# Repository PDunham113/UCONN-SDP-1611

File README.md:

# UCONN SDP 1611

## Summary

* #### Doc
  Contains various documentation and presentation on the project as a whole. This
  has NOT been curated in the slightest. Frankly, the whole project needs a
  little organization.

* #### LCD Daughterboard
  Contains EAGLE files for a graphic LCD and directional pad control. While
  ultimately scrapped, the LCD is electrically functional.

* #### Microcontroller
  Contains EAGLE files for an initial test of the SAMD21 microcontroller circuit.
  The board uses as many through-hole components as possible, and is easily
  assembled by hand. It makes an excellent low-cost substitute to other SAMD21
  development boards, despite its many shortcomings (size, USB functionality).
  Power MUST be applied via the headers, as the USB 5V line is disconnected.

* #### SDP_FIRMWARE
  Contains Arduino code for the latest firmware image for the Solid-State timer
  board. Written for ATSAMD21G18A and requires either the Arduino Zero bootloader
  or compilation by Atmel Studio.

* #### Solid State Relay
  Contains EAGLE files for an initial test of the solid-state relay circuit. The
  board uses as many through-hole components as possible and is easily assembled
  by hand. The board should be able to handle current well in excess of the screw
  terminal ratings, and is fully functional.

* #### Solid-State Timer
  Contains EAGLE files for the primary solid-state timer board. Unlike the former
  tests, this makes use of a significant number of surface mount components and
  requires some patience to assemble. A reflow oven (or toaster oven) is recommended.
  The board supports 8 devices at up to 10A each, and can control each device
  according to a preset sequence up to 240 seconds long in 0.25 second intervals.
  Serial communication over USB is supported for configuration and debugging.

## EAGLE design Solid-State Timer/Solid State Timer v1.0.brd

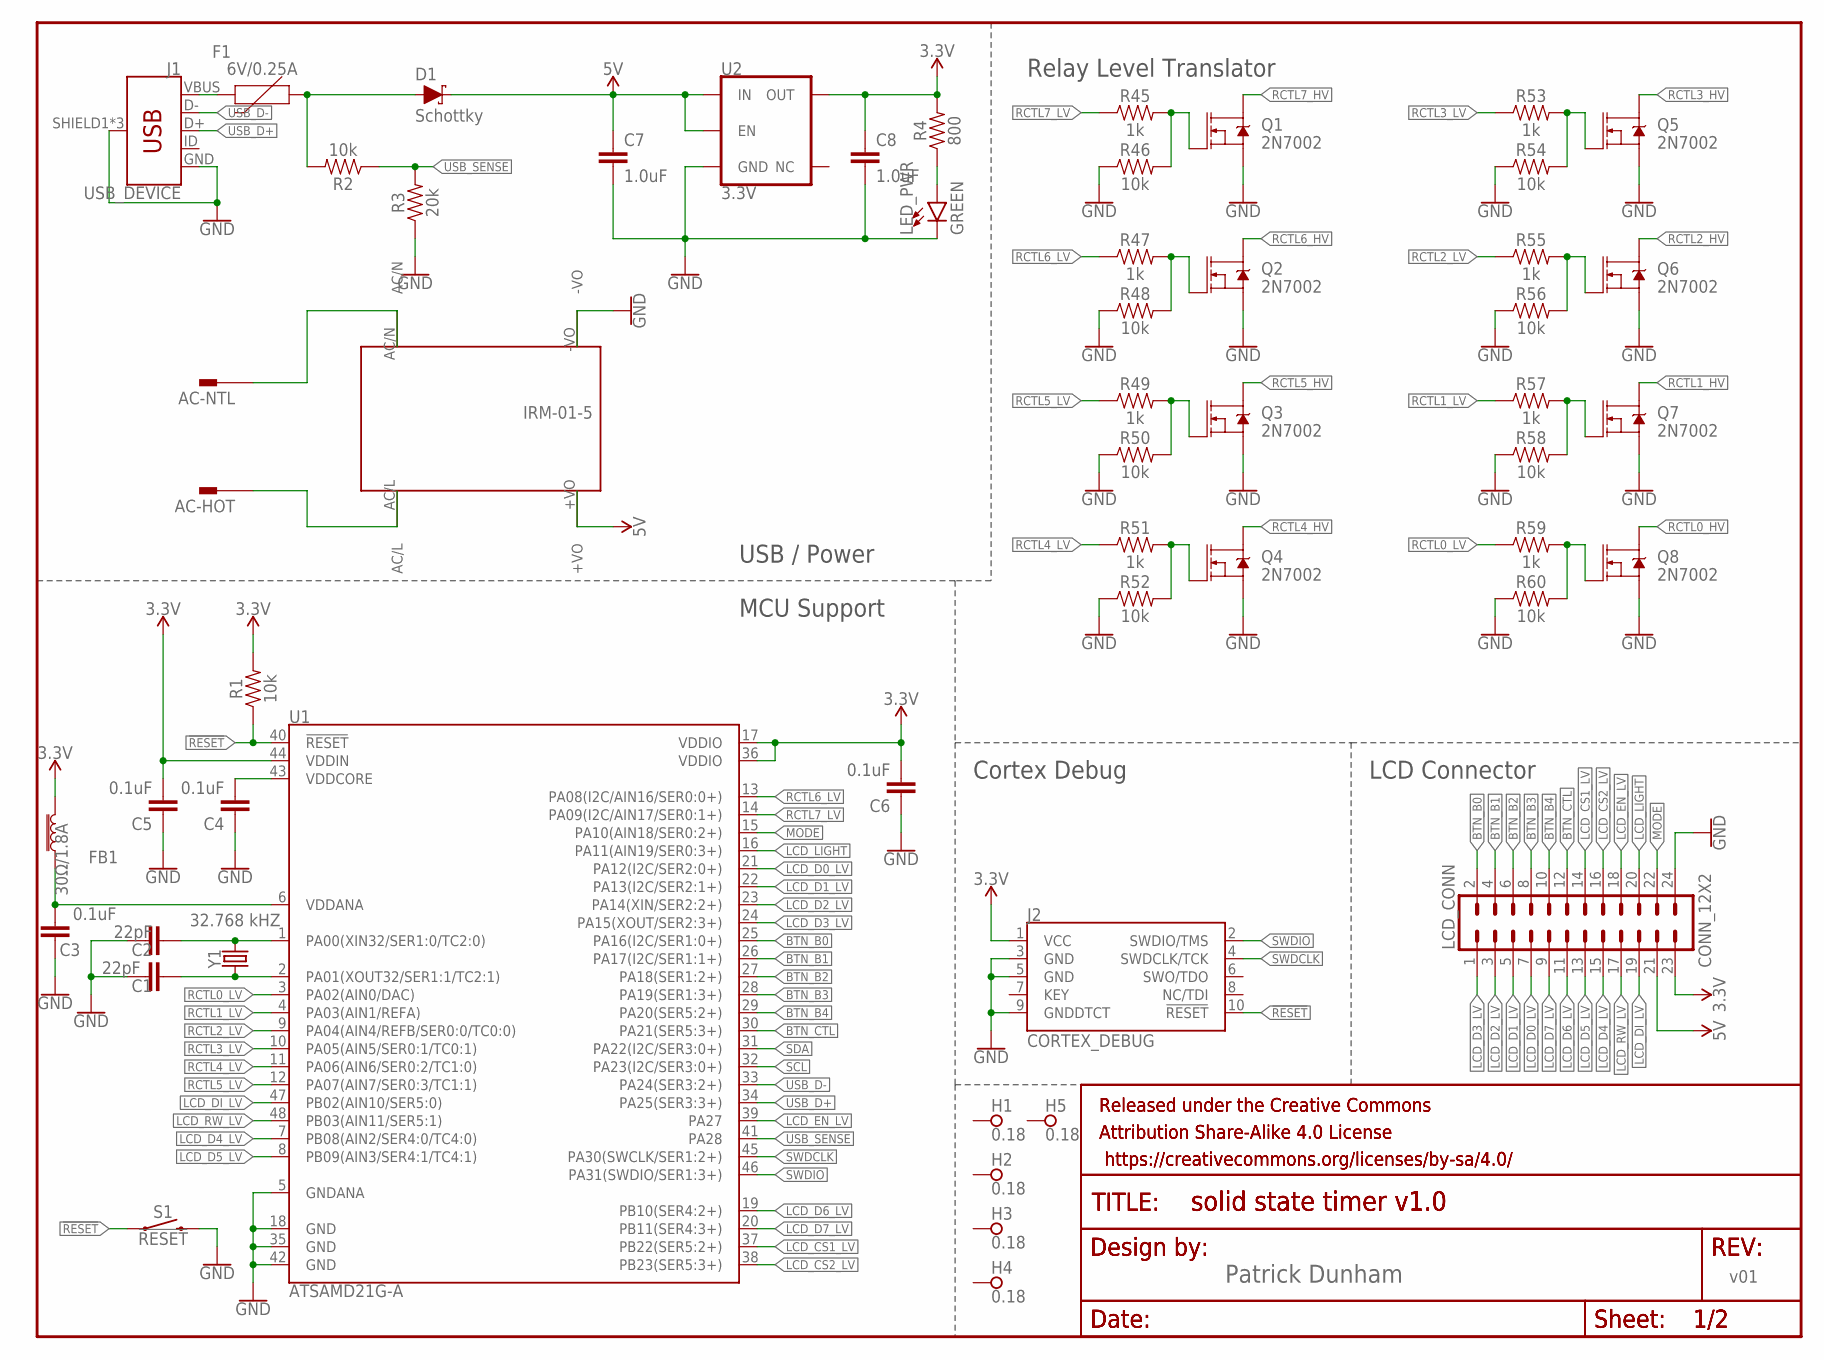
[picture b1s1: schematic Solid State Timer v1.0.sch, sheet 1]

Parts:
AC-HOT: PIN262409-1; 62409-1
AC-NTL: PIN262409-1; 62409-1
C1, C2: 22pF; 0603
C3, C4, C5, C6: 0.1uF; 0603
C7, C8: 1.0uF; 0603
D1: Schottky; SOT23-3
F1: 6V/0.25A; 1206
FB1: 30Ω/1.8A; 0603
FRAME1, FRAME3: FRAME-LETTERNO_PACKAGE; DUMMY
H1, H2, H3, H4, H5: 0.18; PAD_0.1800
J1: USB_DEVICE; USB-B-MICRO-SMD
J2: CORTEX_DEBUG; 2X5-PTH-1.27MM
LCD_CONN: CONN_12X2; 2X12
LED_PWR: GREEN; LED-0603
Q1, Q2, Q3, Q4, Q5, Q6, Q7, Q8: 2N7002; SOT323
R1, R2, R46, R48, R50, R52, R54, R56, R58, R60: 10k; 0603
R3: 20k; 0603
R4: 800; 0603
R45, R47, R49, R51, R53, R55, R57, R59: 1k; 0603
S1: !RESET; TACTILE_SWITCH_PTH_RIGHT_ANGLE_KIT
U1: ATSAMD21G-A; TQFP-48
U2: 3.3V; SOT23-5
U$1: IRM-05-1; IRM-01-5
Y1: 32.768 kHZ; CRYSTAL-SMD-3.2X1.5MM

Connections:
3.3V: C5.2, C6.2, C8.1, FB1.2, J2.1 (VCC), LCD_CONN.23, R1.2, R4.2, U1.17 (VDDIO), U1.36 (VDDIO), U1.44 (VDDIN), U2.5 (OUT); also elsewhere on the board
5V: C7.1, D1.3 (C), LCD_CONN.21, U2.1 (IN), U2.3 (EN), U$1.+VO; also elsewhere on the board
!RESET: J2.10 (!RESET), R1.1, S1.1, U1.40 (!RESET!)
BTN_B0: LCD_CONN.2, U1.25 (PA16(I2C/SER1:0+))
BTN_B1: LCD_CONN.4, U1.26 (PA17(I2C/SER1:1+))
BTN_B2: LCD_CONN.6, U1.27 (PA18(SER1:2+))
BTN_B3: LCD_CONN.8, U1.28 (PA19(SER1:3+))
BTN_B4: LCD_CONN.10, U1.29 (PA20(SER5:2+))
BTN_CTL: LCD_CONN.12, U1.30 (PA21(SER5:3+))
GND: C1.1, C2.1, C3.1, C4.1, C5.1, C6.1, C7.2, C8.2, J1.GND, J1.SHIELD1 (SHIELD), J1.SHIELD2 (SHIELD), J1.SHIELD3 (SHIELD), J2.3 (GND), J2.5 (GND), J2.9 (GNDDTCT), LCD_CONN.24, LED_PWR.C, Q1.2 (S), Q2.2 (S), Q3.2 (S), Q4.2 (S), Q5.2 (S), Q6.2 (S), Q7.2 (S), Q8.2 (S), R3.1, R46.1, R48.1, R50.1, R52.1, R54.1, R56.1, R58.1, R60.1, S1.2, U1.5 (GNDANA), U1.18 (GND), U1.35 (GND), U1.42 (GND), U2.2 (GND), U$1.-VO; also elsewhere on the board
LCD_CS1_LV: LCD_CONN.14, U1.37 (PB22(SER5:2+))
LCD_CS2_LV: LCD_CONN.16, U1.38 (PB23(SER5:3+))
LCD_D0_LV: LCD_CONN.7, U1.21 (PA12(I2C/SER2:0+))
LCD_D1_LV: LCD_CONN.5, U1.22 (PA13(I2C/SER2:1+))
LCD_D2_LV: LCD_CONN.3, U1.23 (PA14(XIN/SER2:2+))
LCD_D3_LV: LCD_CONN.1, U1.24 (PA15(XOUT/SER2:3+))
LCD_D4_LV: LCD_CONN.15, U1.7 (PB08(AIN2/SER4:0/TC4:0))
LCD_D5_LV: LCD_CONN.13, U1.8 (PB09(AIN3/SER4:1/TC4:1))
LCD_D6_LV: LCD_CONN.11, U1.19 (PB10(SER4:2+))
LCD_D7_LV: LCD_CONN.9, U1.20 (PB11(SER4:3+))
LCD_DI_LV: LCD_CONN.19, U1.47 (PB02(AIN10/SER5:0))
LCD_EN_LV: LCD_CONN.18, U1.39 (PA27)
LCD_LIGHT: LCD_CONN.20, U1.16 (PA11(AIN19/SER0:3+))
LCD_RW_LV: LCD_CONN.17, U1.48 (PB03(AIN11/SER5:1))
MODE: LCD_CONN.22, U1.15 (PA10(AIN18/SER0:2+))
unnamed: C2.2, U1.1 (PA00(XIN32/SER1:0/TC2:0)), Y1.P$2 (2)
unnamed: C1.2, U1.2 (PA01(XOUT32/SER1:1/TC2:1)), Y1.P$1 (1)
unnamed: C3.2, FB1.1, U1.6 (VDDANA)
unnamed: C4.2, U1.43 (VDDCORE)
unnamed: F1.2, J1.VBUS
unnamed: AC-NTL.A1, AC-NTL.A2, U$1.AC/N
unnamed: AC-HOT.A1, AC-HOT.A2, U$1.AC/L
unnamed: LED_PWR.A, R4.1
unnamed: Q1.1 (G), R45.2, R46.2
unnamed: D1.1 (A), F1.1, R2.2
unnamed: Q2.1 (G), R47.2, R48.2
unnamed: Q3.1 (G), R49.2, R50.2
unnamed: Q4.1 (G), R51.2, R52.2
unnamed: Q5.1 (G), R53.2, R54.2
unnamed: Q6.1 (G), R55.2, R56.2
unnamed: Q7.1 (G), R57.2, R58.2
unnamed: Q8.1 (G), R59.2, R60.2
RCTL0_HV: Q8.3 (D); also elsewhere on the board
RCTL0_LV: R59.1, U1.3 (PA02(AIN0/DAC))
RCTL1_HV: Q7.3 (D); also elsewhere on the board
RCTL1_LV: R57.1, U1.4 (PA03(AIN1/REFA))
RCTL2_HV: Q6.3 (D); also elsewhere on the board
RCTL2_LV: R55.1, U1.9 (PA04(AIN4/REFB/SER0:0/TC0:0))
RCTL3_HV: Q5.3 (D); also elsewhere on the board
RCTL3_LV: R53.1, U1.10 (PA05(AIN5/SER0:1/TC0:1))
RCTL4_HV: Q4.3 (D); also elsewhere on the board
RCTL4_LV: R51.1, U1.11 (PA06(AIN6/SER0:2/TC1:0))
RCTL5_HV: Q3.3 (D); also elsewhere on the board
RCTL5_LV: R49.1, U1.12 (PA07(AIN7/SER0:3/TC1:1))
RCTL6_HV: Q2.3 (D); also elsewhere on the board
RCTL6_LV: R47.1, U1.13 (PA08(I2C/AIN16/SER0:0+))
RCTL7_HV: Q1.3 (D); also elsewhere on the board
RCTL7_LV: R45.1, U1.14 (PA09(I2C/AIN17/SER0:1+))
SCL: U1.32 (PA23(I2C/SER3:0+)); also elsewhere on the board
SDA: U1.31 (PA22(I2C/SER3:0+)); also elsewhere on the board
SWDCLK: J2.4 (SWDCLK/TCK), U1.45 (PA30(SWCLK/SER1:2+))
SWDIO: J2.2 (SWDIO/TMS), U1.46 (PA31(SWDIO/SER1:3+))
USB_D+: J1.D+, U1.34 (PA25(SER3:3+))
USB_D-: J1.D-, U1.33 (PA24(SER3:2+))
USB_SENSE: R2.1, R3.2, U1.41 (PA28)

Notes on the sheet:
MCU Support
Cortex Debug
USB / Power
LCD Connector
Relay Level Translator

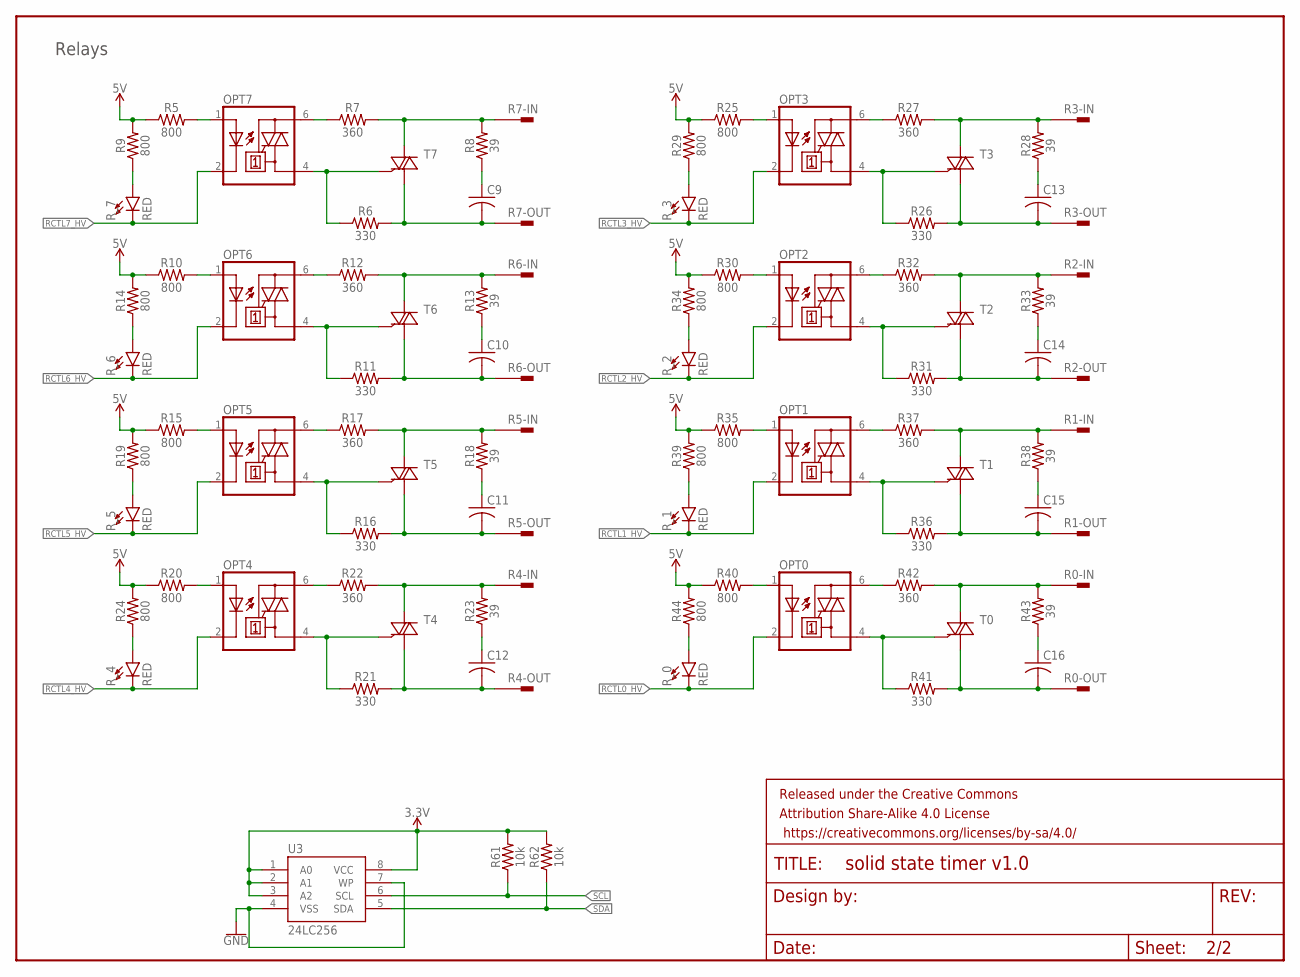
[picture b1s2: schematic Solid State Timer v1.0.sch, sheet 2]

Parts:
C9, C10, C11, C12, C13, C14, C15, C16: C-USC1206; C1206
FRAME2: FRAME-LETTERNO_PACKAGE; DUMMY
OPT0, OPT1, OPT2, OPT3, OPT4, OPT5, OPT6, OPT7: MOC3031M; DIL06
R0-IN, R0-OUT, R1-IN, R1-OUT, R2-IN, R2-OUT, R3-IN, R3-OUT, R4-IN, R4-OUT, R5-IN, R5-OUT, R6-IN, R6-OUT, R7-IN, R7-OUT: PIN262409-1; 62409-1
R5, R9, R10, R14, R15, R19, R20, R24, R25, R29, R30, R34, R35, R39, R40, R44: 800; 0603
R6, R11, R16, R21, R26, R31, R36, R41: 330; 0603
R7, R12, R17, R22, R27, R32, R37, R42: 360; 0603
R8, R13, R18, R23, R28, R33, R38, R43: 39; 0603
R61, R62: 10k; 0603
R_0, R_1, R_2, R_3, R_4, R_5, R_6, R_7: RED; LED-0603
T0, T1, T2, T3, T4, T5, T6, T7: BT138-V; TO220BV
U3: 24LC256; SO08

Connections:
3.3V: R61.2, R62.2, U3.1 (A0), U3.2 (A1), U3.3 (A2), U3.8 (VCC); also elsewhere on the board
5V: R5.1, R9.2, R10.1, R14.2, R15.1, R19.2, R20.1, R24.2, R25.1, R29.2, R30.1, R34.2, R35.1, R39.2, R40.1, R44.2; also elsewhere on the board
GND: U3.4 (VSS), U3.7 (WP); also elsewhere on the board
unnamed: OPT7.1 (A), R5.2
unnamed: OPT7.4 (A1), R6.1, T7.G
unnamed: OPT7.6 (A2), R7.1
unnamed: R7.2, R7-IN.A1, R7-IN.A2, R8.2, T7.T2 (A2)
unnamed: C9.1, R8.1
unnamed: C9.2, R6.2, R7-OUT.A1, R7-OUT.A2, T7.T1 (A1)
unnamed: R9.1, R_7.A
unnamed: OPT6.1 (A), R10.2
unnamed: OPT6.4 (A1), R11.1, T6.G
unnamed: OPT6.6 (A2), R12.1
unnamed: R6-IN.A1, R6-IN.A2, R12.2, R13.2, T6.T2 (A2)
unnamed: C10.1, R13.1
unnamed: C10.2, R6-OUT.A1, R6-OUT.A2, R11.2, T6.T1 (A1)
unnamed: R14.1, R_6.A
unnamed: OPT5.1 (A), R15.2
unnamed: OPT5.4 (A1), R16.1, T5.G
unnamed: OPT5.6 (A2), R17.1
unnamed: R5-IN.A1, R5-IN.A2, R17.2, R18.2, T5.T2 (A2)
unnamed: C11.1, R18.1
unnamed: C11.2, R5-OUT.A1, R5-OUT.A2, R16.2, T5.T1 (A1)
unnamed: R19.1, R_5.A
unnamed: OPT4.1 (A), R20.2
unnamed: OPT4.4 (A1), R21.1, T4.G
unnamed: OPT4.6 (A2), R22.1
unnamed: R4-IN.A1, R4-IN.A2, R22.2, R23.2, T4.T2 (A2)
unnamed: C12.1, R23.1
unnamed: C12.2, R4-OUT.A1, R4-OUT.A2, R21.2, T4.T1 (A1)
unnamed: R24.1, R_4.A
unnamed: OPT3.1 (A), R25.2
unnamed: OPT3.4 (A1), R26.1, T3.G
unnamed: OPT3.6 (A2), R27.1
unnamed: R3-IN.A1, R3-IN.A2, R27.2, R28.2, T3.T2 (A2)
unnamed: C13.1, R28.1
unnamed: R29.1, R_3.A
unnamed: OPT2.1 (A), R30.2
unnamed: OPT2.4 (A1), R31.1, T2.G
unnamed: OPT2.6 (A2), R32.1
unnamed: R2-IN.A1, R2-IN.A2, R32.2, R33.2, T2.T2 (A2)
unnamed: C14.1, R33.1
unnamed: C14.2, R2-OUT.A1, R2-OUT.A2, R31.2, T2.T1 (A1)
unnamed: R34.1, R_2.A
unnamed: OPT1.1 (A), R35.2
unnamed: OPT1.4 (A1), R36.1, T1.G
unnamed: OPT1.6 (A2), R37.1
unnamed: R1-IN.A1, R1-IN.A2, R37.2, R38.2, T1.T2 (A2)
unnamed: C15.1, R38.1
unnamed: C15.2, R1-OUT.A1, R1-OUT.A2, R36.2, T1.T1 (A1)
unnamed: R39.1, R_1.A
unnamed: OPT0.1 (A), R40.2
unnamed: OPT0.4 (A1), R41.1, T0.G
unnamed: OPT0.6 (A2), R42.1
unnamed: R0-IN.A1, R0-IN.A2, R42.2, R43.2, T0.T2 (A2)
unnamed: C16.1, R43.1
unnamed: C16.2, R0-OUT.A1, R0-OUT.A2, R41.2, T0.T1 (A1)
unnamed: R44.1, R_0.A
R3-OUT: C13.2, R3-OUT.A1, R3-OUT.A2, R26.2, T3.T1 (A1)
RCTL0_HV: OPT0.2 (C), R_0.C; also elsewhere on the board
RCTL1_HV: OPT1.2 (C), R_1.C; also elsewhere on the board
RCTL2_HV: OPT2.2 (C), R_2.C; also elsewhere on the board
RCTL3_HV: OPT3.2 (C), R_3.C; also elsewhere on the board
RCTL4_HV: OPT4.2 (C), R_4.C; also elsewhere on the board
RCTL5_HV: OPT5.2 (C), R_5.C; also elsewhere on the board
RCTL6_HV: OPT6.2 (C), R_6.C; also elsewhere on the board
RCTL7_HV: OPT7.2 (C), R_7.C; also elsewhere on the board
SCL: R61.1, U3.6 (SCL); also elsewhere on the board
SDA: R62.1, U3.5 (SDA); also elsewhere on the board

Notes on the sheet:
Relays

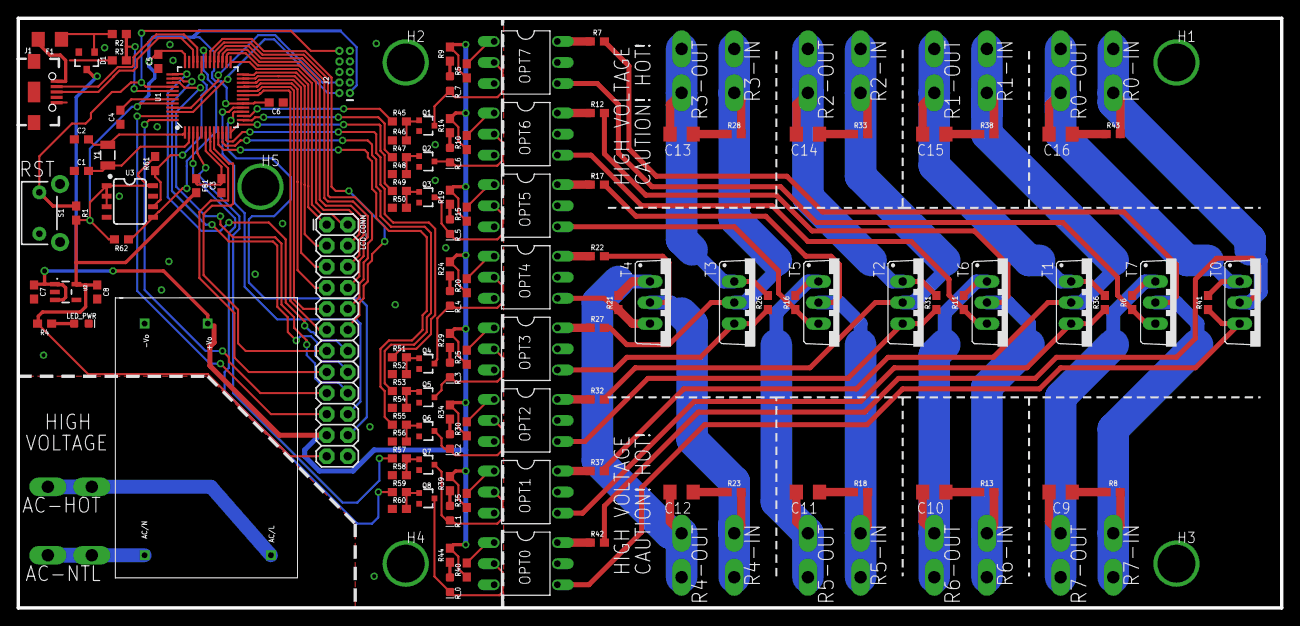
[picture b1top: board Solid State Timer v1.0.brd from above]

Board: 2 copper layers, 152.4 x 71.1 mm, 149 parts (0 on the bottom side), 121 nets.

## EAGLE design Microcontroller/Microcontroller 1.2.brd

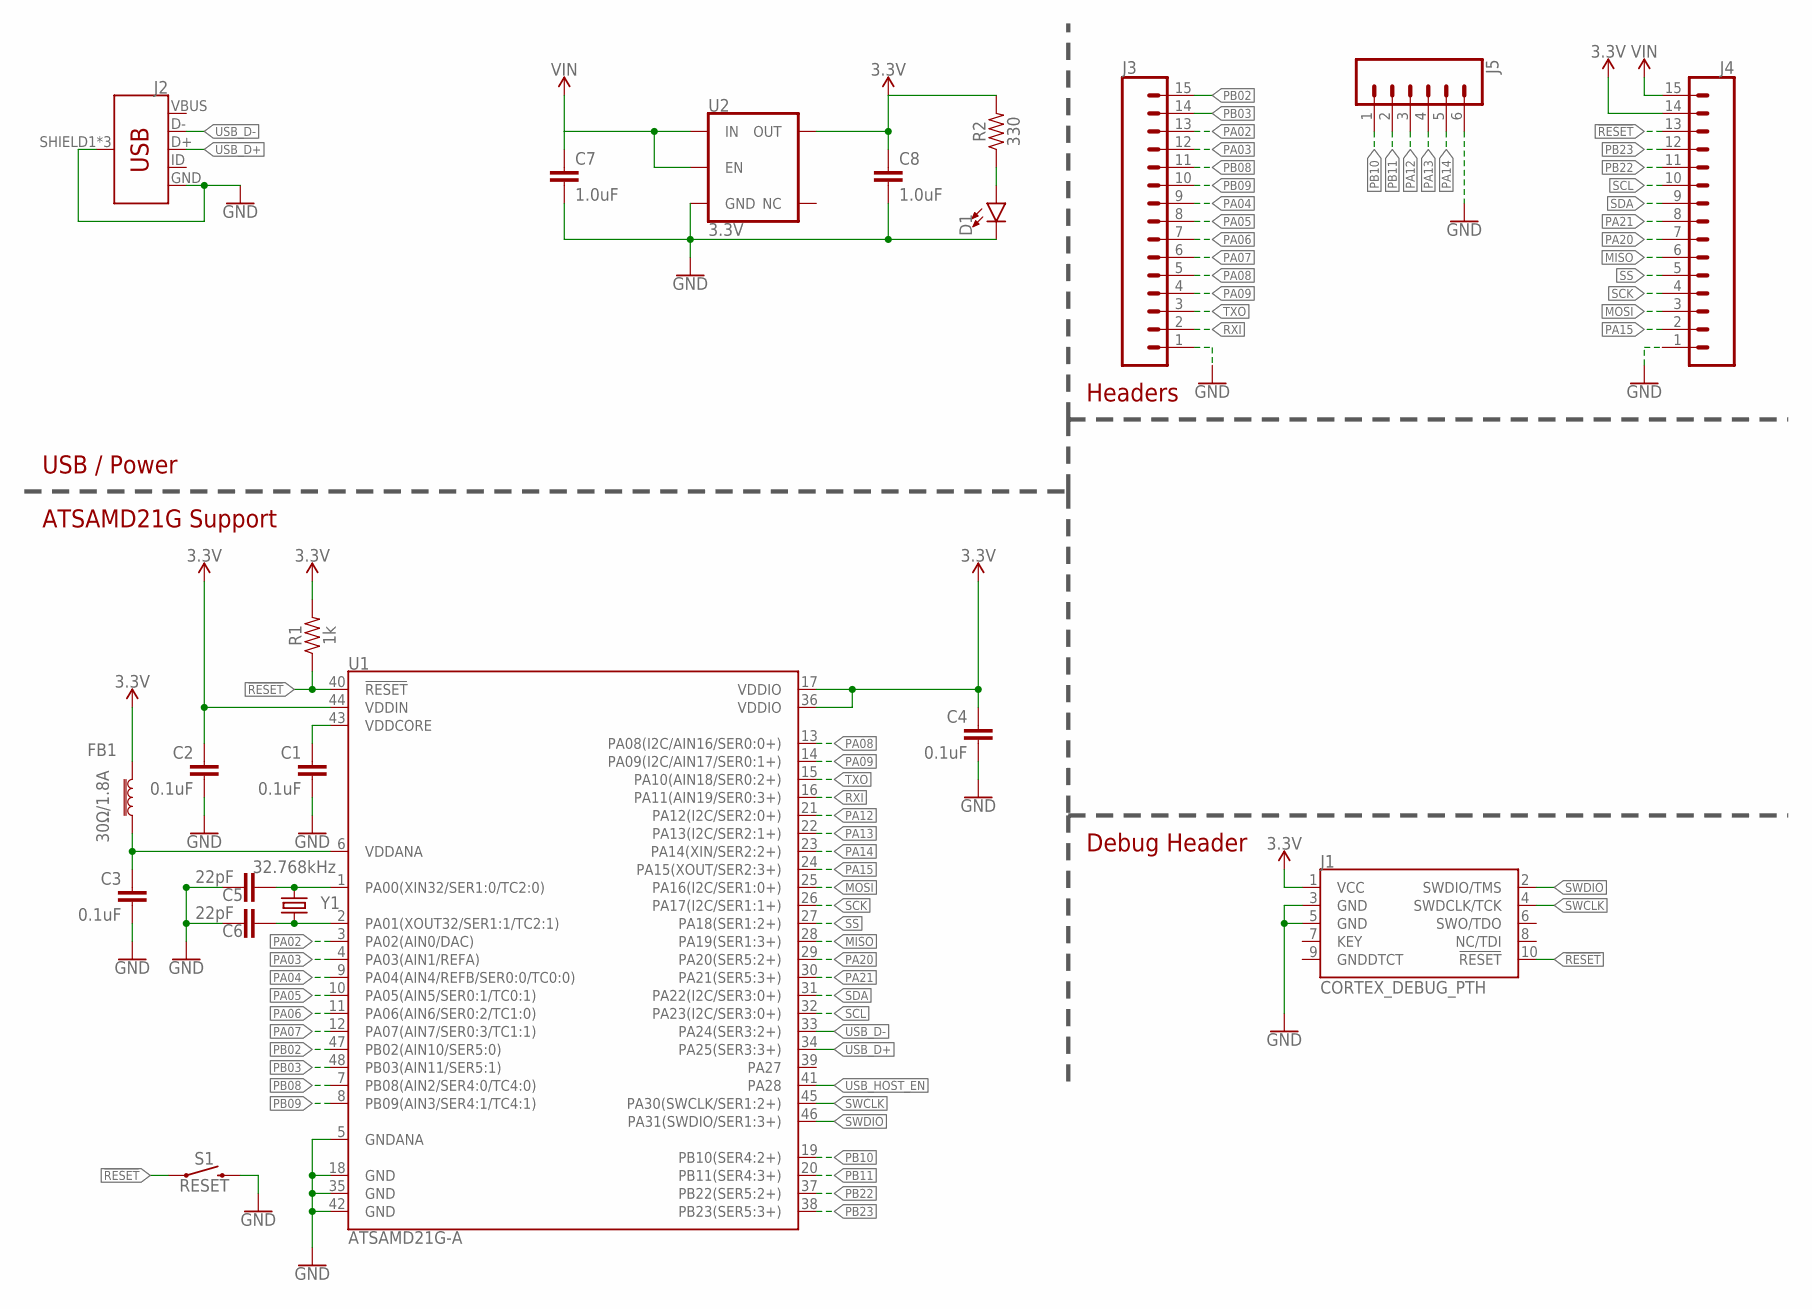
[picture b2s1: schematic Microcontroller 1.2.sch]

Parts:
C1, C2, C3, C4: 0.1uF; CAP-PTH-SMALL-KIT
C5, C6: 22pF; CAP-PTH-SMALL-KIT
C7, C8: 1.0uF; CAP-PTH-SMALL-KIT
D1: LED5MM; LED_5MM
FB1: 30Ω/1.8A; 0603
J1: CORTEX_DEBUG_PTH; 2X5-PTH-1.27MM
J2: USB_MICRO-B_FEMALE-SMT; USB-B-MICRO-SMD
J3, J4: CONN_15LOCK; 1X15_LOCK
J5: CONN_06LOCK; 1X06_LOCK
R1: 1k; AXIAL-0.3
R2: 330; AXIAL-0.3
S1: RESET; TACTILE_SWITCH_PTH_RIGHT_ANGLE_KIT
U1: ATSAMD21G-A; TQFP-48
U2: 3.3V; SOT23-5
Y1: 32.768kHz; CRYSTAL-PTH-2X6-CYL

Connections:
3.3V: C2.1, C4.1, C8.1, FB1.1, J1.1 (VCC), J4.14, R1.P$2 (2), R2.P$2 (2), U1.17 (VDDIO), U1.36 (VDDIO), U1.44 (VDDIN), U2.5 (OUT)
!RESET: J1.10 (!RESET), J4.13, R1.P$1 (1), S1.1, U1.40 (!RESET!)
GND: C1.2, C2.2, C3.2, C4.2, C5.1, C6.1, C7.2, C8.2, D1.K (C), J1.3 (GND), J1.5 (GND), J2.GND, J2.SHIELD1 (SHIELD), J2.SHIELD2 (SHIELD), J2.SHIELD3 (SHIELD), J3.1, J4.1, J5.6, S1.2, U1.5 (GNDANA), U1.18 (GND), U1.35 (GND), U1.42 (GND), U2.2 (GND)
MISO: J4.6, U1.28 (PA19(SER1:3+))
MOSI: J4.3, U1.25 (PA16(I2C/SER1:0+))
unnamed: C1.1, U1.43 (VDDCORE)
unnamed: C6.2, U1.2 (PA01(XOUT32/SER1:1/TC2:1)), Y1.1
unnamed: C3.1, FB1.2, U1.6 (VDDANA)
unnamed: C5.2, U1.1 (PA00(XIN32/SER1:0/TC2:0)), Y1.2
unnamed: D1.A, R2.P$1 (1)
PA02: J3.13, U1.3 (PA02(AIN0/DAC))
PA03: J3.12, U1.4 (PA03(AIN1/REFA))
PA04: J3.9, U1.9 (PA04(AIN4/REFB/SER0:0/TC0:0))
PA05: J3.8, U1.10 (PA05(AIN5/SER0:1/TC0:1))
PA06: J3.7, U1.11 (PA06(AIN6/SER0:2/TC1:0))
PA07: J3.6, U1.12 (PA07(AIN7/SER0:3/TC1:1))
PA08: J3.5, U1.13 (PA08(I2C/AIN16/SER0:0+))
PA09: J3.4, U1.14 (PA09(I2C/AIN17/SER0:1+))
PA12: J5.3, U1.21 (PA12(I2C/SER2:0+))
PA13: J5.4, U1.22 (PA13(I2C/SER2:1+))
PA14: J5.5, U1.23 (PA14(XIN/SER2:2+))
PA15: J4.2, U1.24 (PA15(XOUT/SER2:3+))
PA20: J4.7, U1.29 (PA20(SER5:2+))
PA21: J4.8, U1.30 (PA21(SER5:3+))
PB02: J3.15, U1.47 (PB02(AIN10/SER5:0))
PB03: J3.14, U1.48 (PB03(AIN11/SER5:1))
PB08: J3.11, U1.7 (PB08(AIN2/SER4:0/TC4:0))
PB09: J3.10, U1.8 (PB09(AIN3/SER4:1/TC4:1))
PB10: J5.1, U1.19 (PB10(SER4:2+))
PB11: J5.2, U1.20 (PB11(SER4:3+))
PB22: J4.11, U1.37 (PB22(SER5:2+))
PB23: J4.12, U1.38 (PB23(SER5:3+))
RXI: J3.2, U1.16 (PA11(AIN19/SER0:3+))
SCK: J4.4, U1.26 (PA17(I2C/SER1:1+))
SCL: J4.10, U1.32 (PA23(I2C/SER3:0+))
SDA: J4.9, U1.31 (PA22(I2C/SER3:0+))
SS: J4.5, U1.27 (PA18(SER1:2+))
SWCLK: J1.4 (SWDCLK/TCK), U1.45 (PA30(SWCLK/SER1:2+))
SWDIO: J1.2 (SWDIO/TMS), U1.46 (PA31(SWDIO/SER1:3+))
TXO: J3.3, U1.15 (PA10(AIN18/SER0:2+))
USB_D+: J2.D+, U1.34 (PA25(SER3:3+))
USB_D-: J2.D-, U1.33 (PA24(SER3:2+))
USB_HOST_EN: U1.41 (PA28)
VBUS: J2.VBUS
VIN: C7.1, J4.15, U2.1 (IN), U2.3 (EN)

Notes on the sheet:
ATSAMD21G Support
Debug Header
Headers
USB / Power

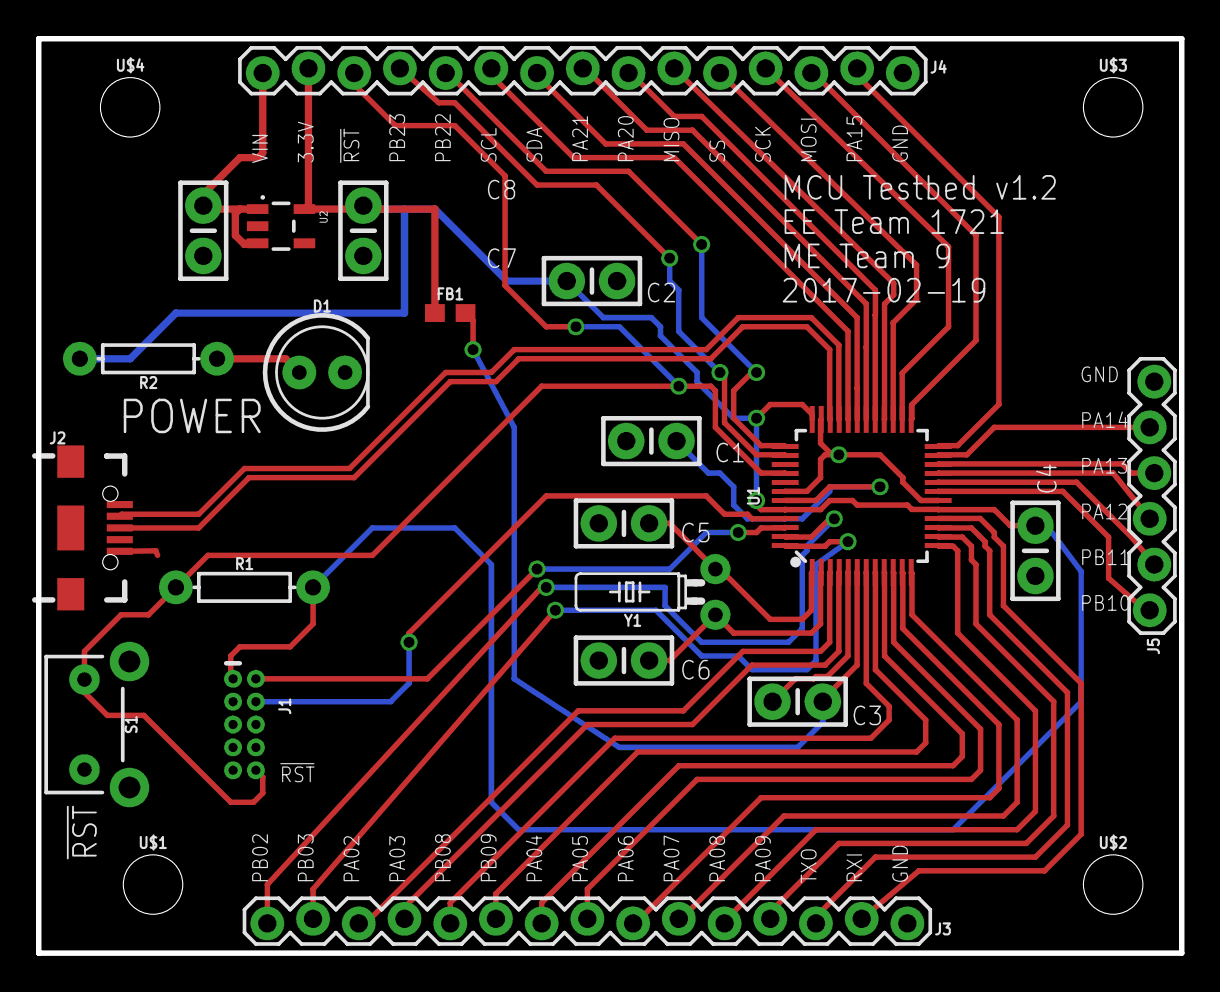
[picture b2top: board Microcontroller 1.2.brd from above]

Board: 2 copper layers, 63.5 x 50.8 mm, 25 parts (0 on the bottom side), 43 nets.

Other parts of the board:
U$1, U$2, U$3, U$4: STAND-OFF

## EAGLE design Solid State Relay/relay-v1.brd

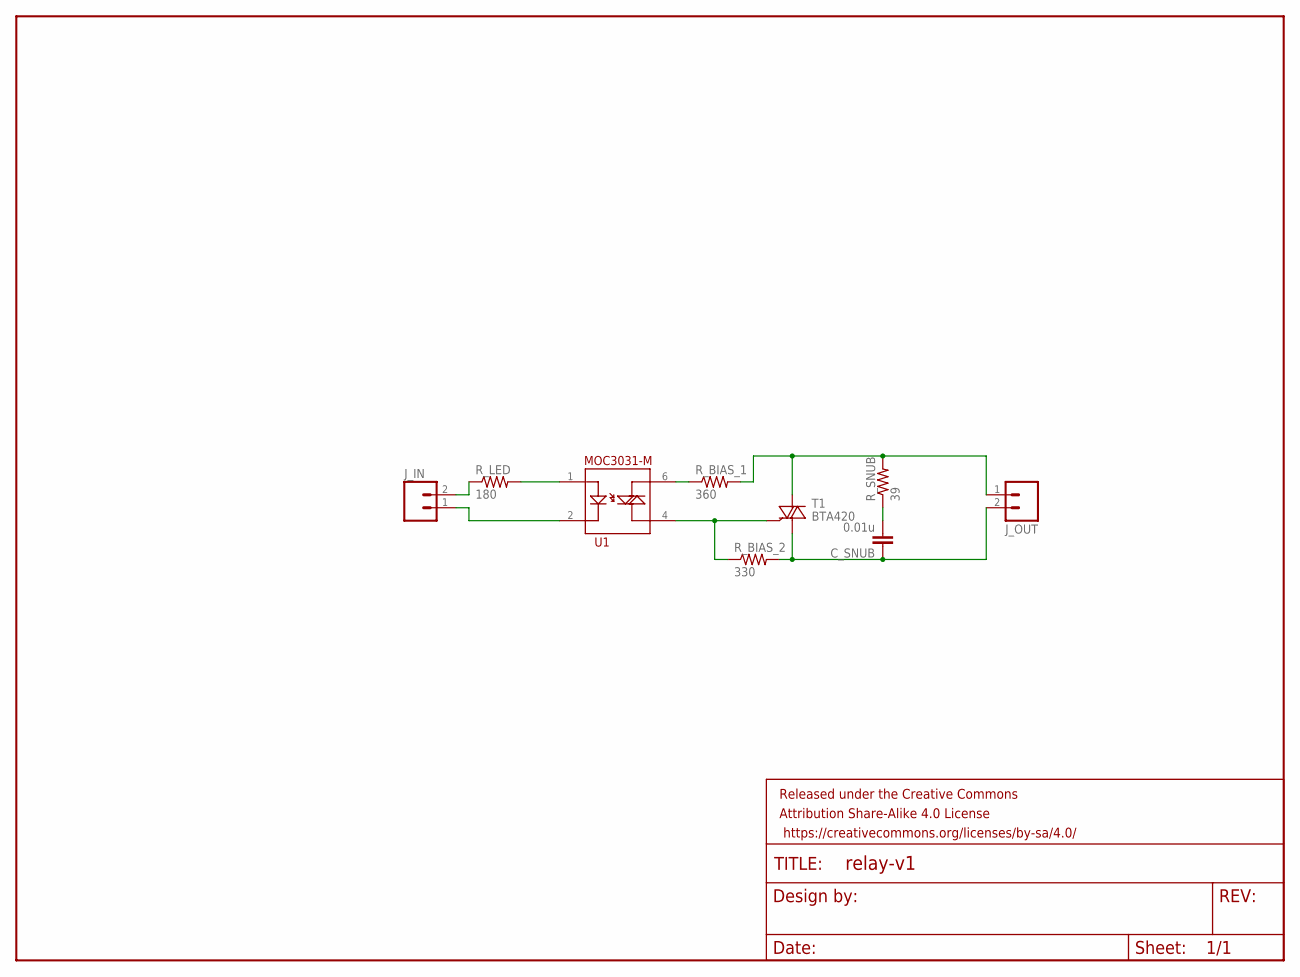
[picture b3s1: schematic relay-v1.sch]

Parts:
C_SNUB: 0.01u; CAP-PTH-SMALLEZ
FRAME1: FRAME-LETTERNO_PACKAGE; DUMMY
J_IN: M02PTH; 1X02
J_OUT: M025MM; SCREWTERMINAL-5MM-2
R_BIAS_1: 360; AXIAL-0.4
R_BIAS_2: 330; AXIAL-0.4
R_LED: 180; AXIAL-0.4
R_SNUB: 39; AXIAL-0.4
T1: BTA420; TO220BV
U1: MOC3063M; DIL06

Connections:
DEVICE: J_OUT.1, R_BIAS_1.P$2 (2), R_SNUB.P$2 (2), T1.T2 (A2)
LED_MINUS: J_IN.1, U1.2
LED_PLUS: J_IN.2, R_LED.P$1 (1)
unnamed: R_LED.P$2 (2), U1.1
unnamed: R_BIAS_1.P$1 (1), U1.6
unnamed: R_BIAS_2.P$1 (1), T1.G, U1.4
unnamed: C_SNUB.2, R_SNUB.P$1 (1)
POWER: C_SNUB.1, J_OUT.2, R_BIAS_2.P$2 (2), T1.T1 (A1)

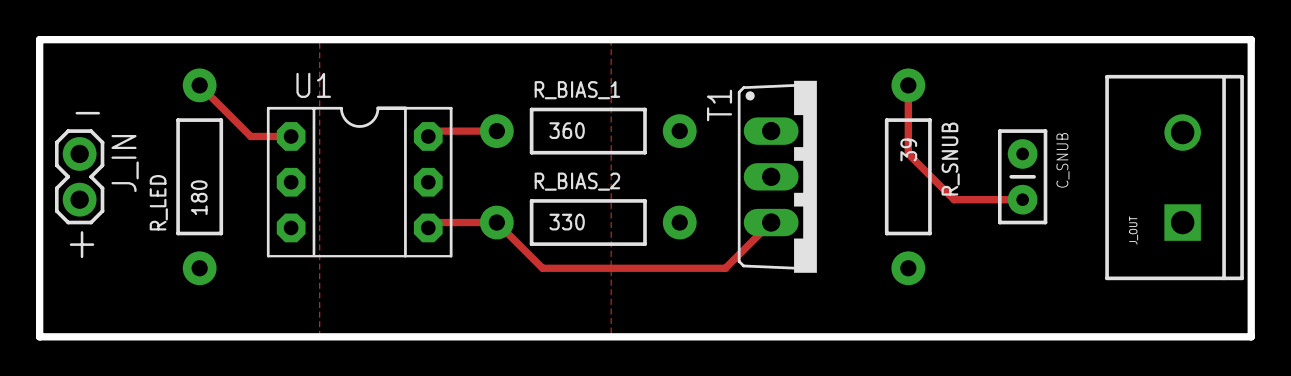
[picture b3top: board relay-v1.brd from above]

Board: 2 copper layers, 67.3 x 16.5 mm, 10 parts (0 on the bottom side), 8 nets.

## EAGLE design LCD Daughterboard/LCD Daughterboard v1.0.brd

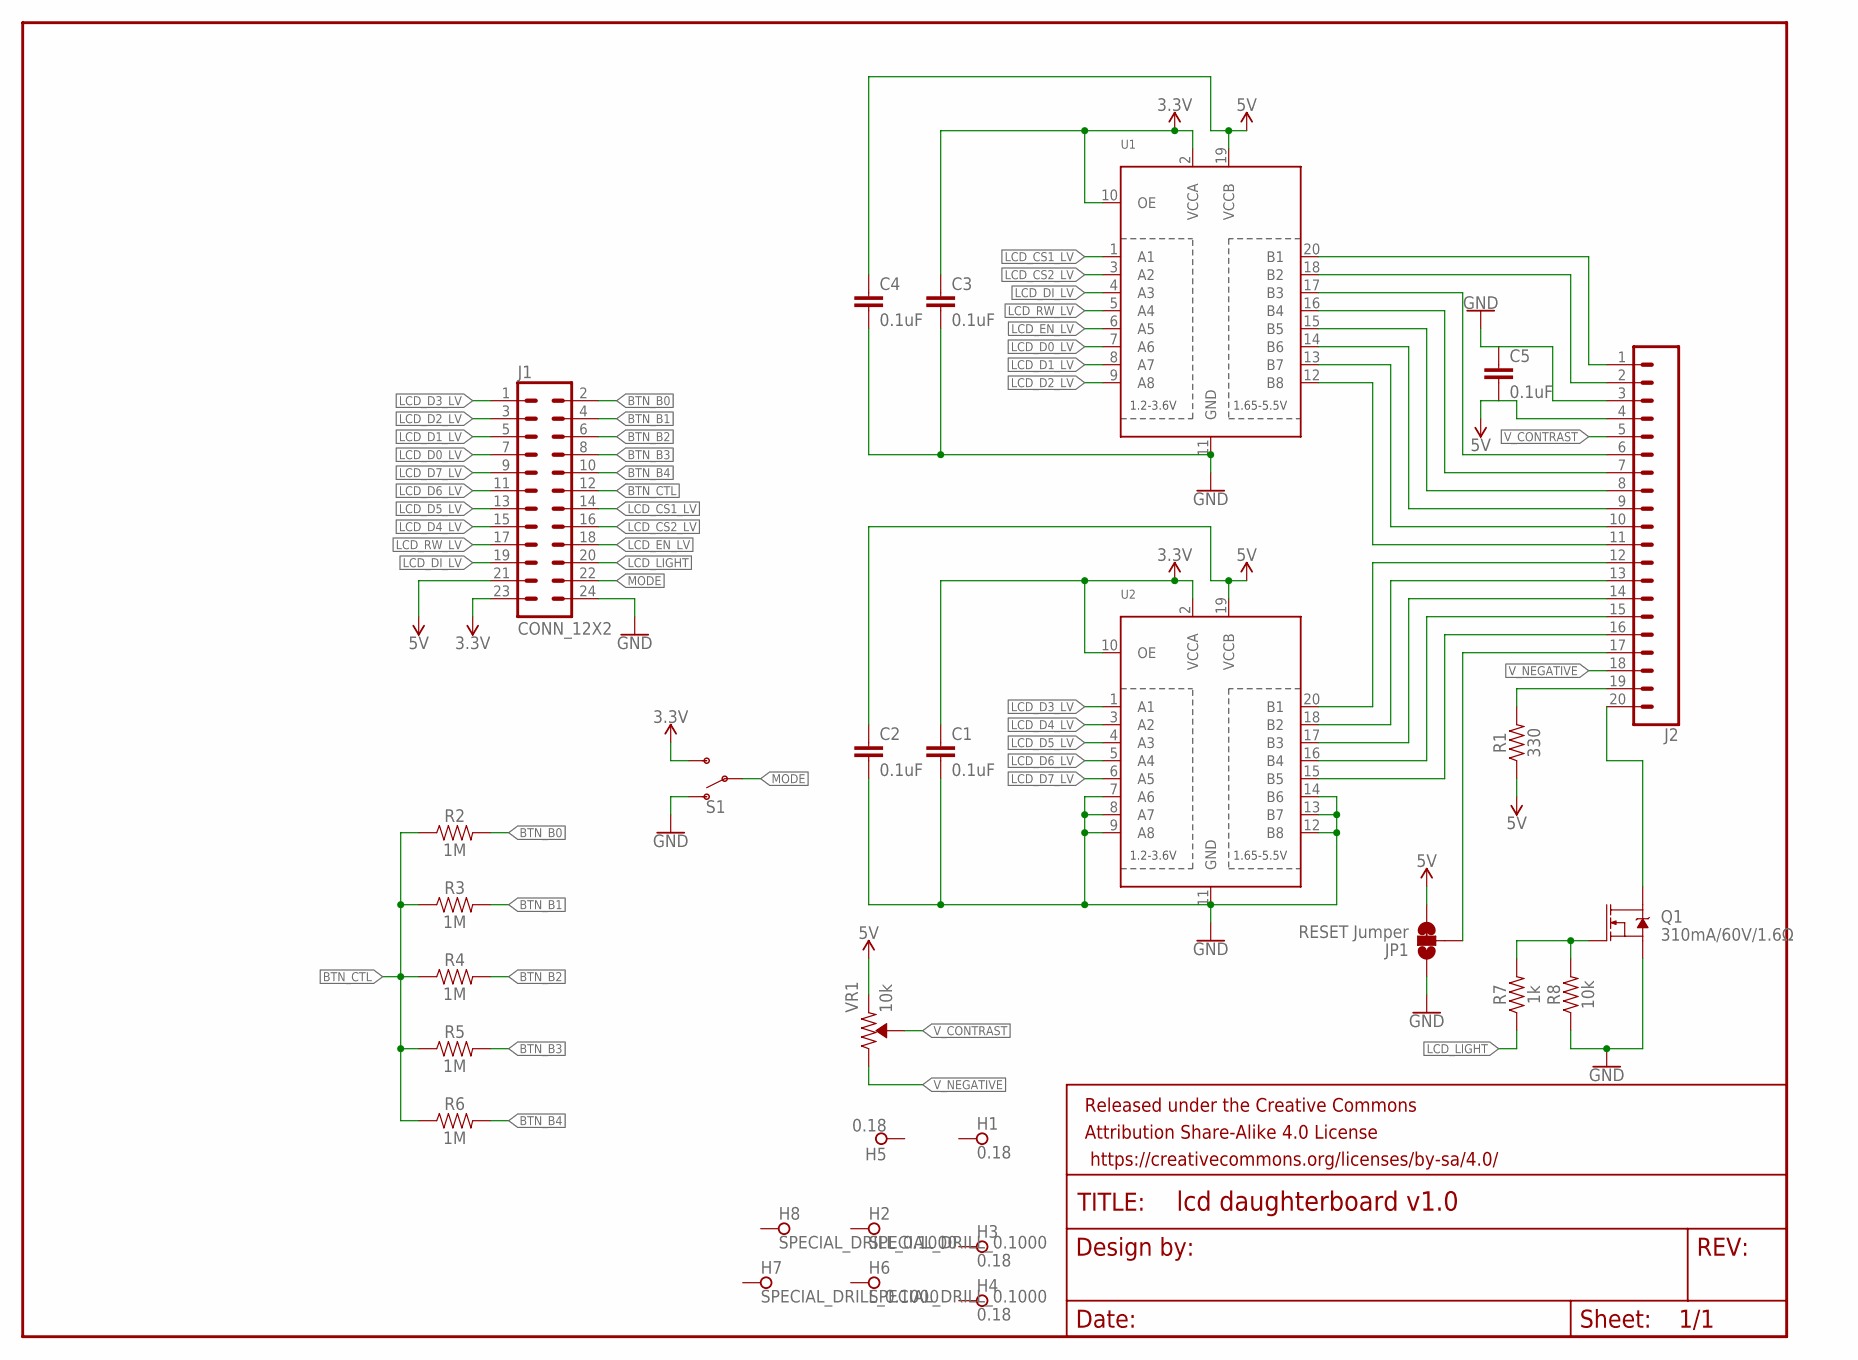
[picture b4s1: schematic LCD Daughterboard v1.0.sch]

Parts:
C1, C2, C3, C4, C5: 0.1uF; 0603
FRAME1: FRAME-LETTERNO_PACKAGE; DUMMY
H1, H3, H4, H5: 0.18; PAD_0.1800
H2, H6, H7, H8: SPECIAL_DRILL_0.1000; PAD_0.1000
J1: CONN_12X2; 2X12
J2: CONN_20LOCK; 1X20_LOCK
JP1: RESET Jumper; SMT-JUMPER_3_1-NC_TRACE_SILK
Q1: 310mA/60V/1.6Ω; SOT323
R1: 330; 0603
R2, R3, R4, R5, R6: 1M; 0603
R7: 1k; 0603
R8: 10k; 0603
S1: SWITCH-SPDT-PTH-11.6X4.0MM; SWITCH_SPDT_PTH_11.6X4.0MM
U1, U2: TXB0108PWR; TSSOP20
VR1: 10k; TRIMPOT-PTH-3386U

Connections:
3.3V: C1.1, C3.1, J1.23, S1.3 (S), U1.2 (VCCA), U1.10 (OE), U2.2 (VCCA), U2.10 (OE)
5V: C2.1, C4.1, C5.2, J1.21, J2.4, JP1.3, R1.1, U1.19 (VCCB), U2.19 (VCCB), VR1.1 (CCW)
BTN_B0: J1.2, R2.2
BTN_B1: J1.4, R3.2
BTN_B2: J1.6, R4.2
BTN_B3: J1.8, R5.2
BTN_B4: J1.10, R6.2
BTN_CTL: J1.12, R2.1, R3.1, R4.1, R5.1, R6.1
GND: C1.2, C2.2, C3.2, C4.2, C5.1, J1.24, J2.3, JP1.1, Q1.2 (S), R8.1, S1.1 (O), U1.11 (GND), U2.7 (A6), U2.8 (A7), U2.9 (A8), U2.11 (GND), U2.12 (B8), U2.13 (B7), U2.14 (B6)
LCD_CS1_LV: J1.14, U1.1 (A1)
LCD_CS2_LV: J1.16, U1.3 (A2)
LCD_D0_LV: J1.7, U1.7 (A6)
LCD_D1_LV: J1.5, U1.8 (A7)
LCD_D2_LV: J1.3, U1.9 (A8)
LCD_D3_LV: J1.1, U2.1 (A1)
LCD_D4_LV: J1.15, U2.3 (A2)
LCD_D5_LV: J1.13, U2.4 (A3)
LCD_D6_LV: J1.11, U2.5 (A4)
LCD_D7_LV: J1.9, U2.6 (A5)
LCD_DI_LV: J1.19, U1.4 (A3)
LCD_EN_LV: J1.18, U1.6 (A5)
LCD_LIGHT: J1.20, R7.1
LCD_RW_LV: J1.17, U1.5 (A4)
MODE: J1.22, S1.2
unnamed: J2.1, U1.20 (B1)
unnamed: J2.2, U1.18 (B2)
unnamed: J2.6, U1.17 (B3)
unnamed: J2.7, U1.16 (B4)
unnamed: J2.8, U1.15 (B5)
unnamed: J2.9, U1.14 (B6)
unnamed: J2.10, U1.13 (B7)
unnamed: J2.11, U1.12 (B8)
unnamed: J2.19, R1.2
unnamed: J2.20, Q1.3 (D)
unnamed: J2.12, U2.20 (B1)
unnamed: J2.13, U2.18 (B2)
unnamed: J2.14, U2.17 (B3)
unnamed: J2.15, U2.16 (B4)
unnamed: J2.16, U2.15 (B5)
unnamed: J2.17, JP1.2
unnamed: Q1.1 (G), R7.2, R8.2
V_CONTRAST: J2.5, VR1.2 (WIPER)
V_NEGATIVE: J2.18, VR1.3 (CW)

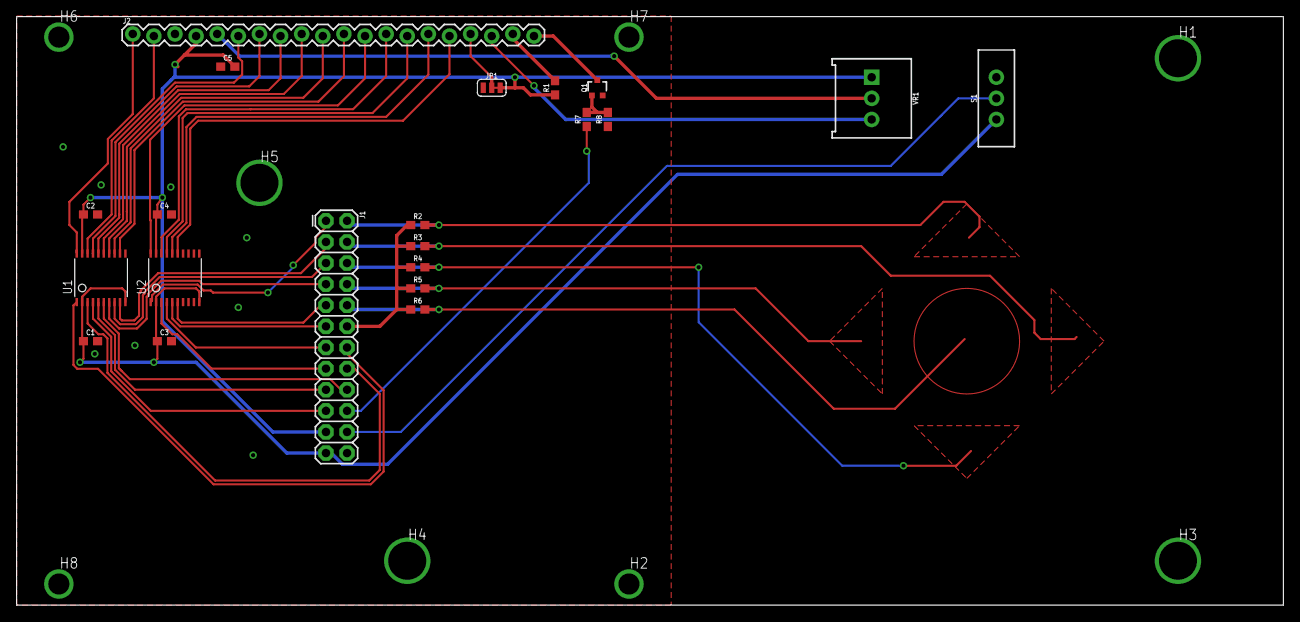
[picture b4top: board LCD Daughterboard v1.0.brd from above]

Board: 2 copper layers, 152.4 x 70.8 mm, 30 parts (0 on the bottom side), 43 nets.

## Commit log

2018-01-10 Initial commit
    Added all schematics, board files, and firmware, as well as summary readme.
2018-01-10 Added documentation
    Added terribly disorganized documentation
2018-01-10 More docs

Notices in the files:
parts and their libraries:
SparkFun-Connectors: Licensing: Creative Commons ShareAlike 4.0 International - https://creativecommons.org/licenses/by-sa/4.0
SparkFun-Aesthetics: Released under the Creative Commons Attribution Share-Alike 4.0 License
SparkFun-Aesthetics: https://creativecommons.org/licenses/by-sa/4.0
